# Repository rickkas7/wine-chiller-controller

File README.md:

# Wine chiller controller replacement

I have two Edgestar TWR282S thermoelectric wine chillers. One has wine in it, but the other I keep vegetables in, sort of like a root cellar.

They're over 10 years old, and I've been replacing parts on them for a while, but the case and doors are fine and the vegetable one has custom plexiglass shelves in it, so I hesitate to replace it.

I've replaced interior fans, [exterior fans](http://blog.rickk.com/food/2014/12/wine-chiller-exterior-fan-repair.html), and [Peltier chillers](http://blog.rickk.com/food/2013/06/repairing-a-wine-chiller.html), which are all pretty straightforward to do.

I also replaced the [controller boards](http://blog.rickk.com/food/2013/10/repairing-a-wine-chiller-part-2.html), which were available from Edgestar. They were kind of expensive at $48, and apparently not very durable, because one of the 4 year old replacements failed. And they're no longer available.

It appears the inductor failed. I might be able to just replace that but I have a better idea.

I added a new power supply, controller board, and a fancy display that shows the temperature and also communicates the data so I can monitor the temperatures remotely!

The cyan LED to the right of the alphanumeric display turns red when the temperature is out of normal range.

I also get push notifications on my phone if the temperature goes way out of normal range.

## Power Supply

I replaced the power supply with a $14.98 12V 10A switching power supply that I got [from Amazon](https://www.amazon.com/LEDMO-Switching-Converter-Adapter-Transformer/dp/B01E6RMASC/ref=pd_ybh_a_4). It really only needs to be 5 to 6A, but the 10A was reasonably priced and offers a nice safety margin.

I was able to use the existing power cord, and I just replaced the connector with two spade lugs for connecting to the power supply. I also moved it from above the Peltier heat sink to the side, so hot air is not constantly blowing across it. The old location really seems suboptimal.

## Power Board

I made a power/controller board as well. It has a power supply for the display board, a bunch of handy connectors, a fuse, and a relay. 

In practice the Peltier is always on in my experience, but I did add a relay so it could be turned off in software, based on the thermometer reading inside the chiller. This allows for temperature control, and would also save some energy, as the Peltier by far uses the most energy, about 48 watts.

This is the controller board with the 7 SMD components soldered to the board.

And with all of the through-hole components soldered on.

Installed in the chiller.

## Temperature sensor

I drilled a hole through the back of the chiller and used a weatherproof DS18B20 temperature sensor [from Amazon](https://www.amazon.com/Hilitchi-DS18B20-Waterproof-Temperature-Sensors/dp/B018KFX5X0/ref=sr_1_5). It was $12.99 for a set of 5 but I only needed 1 for this project.

## Interior connections

Above the temperature sensor is the wiring that goes to the interior control box. There is one connector with 2 red wires and a black. And another connector with a black and yellow.

Connect all of the reds together; these are the +12V to the light and interior fan.

Connect all of the blacks together; these are the GND to the light and interior fan.

The yellow wire is for the temperature control inside; that's not used.

The light switch still works.

## Display board

The display board is mounted on the front of the chiller.

Here's the display board with only the SMD components mounted. These include another DS18B20 temperature sensor (this time a 8-SOIC version) and a 4.7K pull-up resistor (0603 SMD) for the 1-Wire interface.

It also has a NeoPixel (WS2812) programmable LED and a 470 ohm series resistor for the data line (0603 SMD).

And power supply capacitors 0.1uF and 10 uF, and the SMD socket for the Particle Photon.

There are also through-hole connectors for a modular jack and a SSD1306 display.

## Total Materials

This did cost more than the original controller, but it has a lot more features. In reality, you can just buy the power supply and wire it up with wire nuts and a little wire and it would cost maybe $16.

| Item | Source | Price |
|---|---|---|
| Power Supply | [Amazon](https://www.amazon.com/LEDMO-Switching-Converter-Adapter-Transformer/dp/B01E6RMASC/ref=pd_ybh_a_4) | 14.98 |
| Spade Lugs (2) | | $0.20<sup>1</sup> |
| ChillerPower Board | [OshPark](https://oshpark.com) | $4.90<sup>2</sup> |
| 2-conductor terminal blocks (3) | [DigiKey](https://www.digikey.com/product-detail/en/on-shore-technology-inc/OSTTF020161/ED2623-ND/614572) | $2.55 |
| 3-conductor terminal block | [DigiKey](https://www.digikey.com/product-detail/en/on-shore-technology-inc/OSTTE030161/ED2636-ND/614585) | $1.00 | 
| Modular Jack | [DigiKey](https://www.digikey.com/product-detail/en/stewart-connector/SS-7066-NF/380-1043-ND/388305) | $0.77 |
| Fuse holder | [DigiKey](https://www.digikey.com/product-detail/en/keystone-electronics/3568/36-3568-ND/2137306) | $0.98 |
| Fuse MiniATC 7.5A |  | $0.76<sup>1</sup> |
| Capacitor 10 uF 0805 | [DigiKey](https://www.digikey.com/product-detail/en/murata-electronics-north-america/GRM21BR61C106KE15L/490-3886-1-ND/965928) | $0.07<sup>4</sup> |
| Capacitor 0.1 uF | [DigiKey](https://www.digikey.com/product-detail/en/murata-electronics-north-america/GRM188R71C104KA01D/490-1532-1-ND/587771) | $0.03<sup>3</sup> |
| Resistor 680 ohm 0805 | [DigiKey](https://www.digikey.com/product-detail/en/panasonic-electronic-components/ERJ-6GEYJ681V/P680ACT-ND/90033) | $0.01<sup>3</sup> |
| Green LED 0603 | [DigiKey](https://www.digikey.com/product-detail/en/lite-on-inc/LTST-C193KGKT-5A/160-1828-1-ND/2356247) | $0.23<sup>5</sup> |
| Relay | [DigiKey](https://www.digikey.com/product-detail/en/panasonic-electric-works/JS1-5V-F/255-2064-ND/1242012) | $1.63 |
| Diode BAS21 | [DigiKey](http://www.digikey.com/product-detail/en/BAS21-7-F/BAS21-FDICT-ND/717813) | $0.14 |
| 2N7002 MOSFET | [DigiKey](https://www.digikey.com/product-detail/en/on-semiconductor/2N7002LT3G/2N7002LT3GOSCT-ND/2704932) | $0.16 |
| R-78-E Regulator | [DigiKey](https://www.digikey.com/product-detail/en/recom-power/R-78E5.0-0.5/945-1648-5-ND/2834904) | $2.84 |
| DS18B20 Weatherproof | [Amazon](https://www.amazon.com/Hilitchi-DS18B20-Waterproof-Temperature-Sensors/dp/B018KFX5X0/ref=sr_1_5) | $2.99<sup>6</sup> |
| ChillerDisplay Board | [OshPark](https://oshpark.com) | $8.31<sup>8</sup> |
| Photon Headers (2) | [DigiKey](https://www.digikey.com/product-detail/en/sullins-connector-solutions/NPTC121KFXC-RC/S5604-ND/776062) | $3.38 |
| Particle Photon | [Amazon](https://www.amazon.com/Particle-PHOTON-Comprehensive-Development-Access/dp/B016YNU1A0/ref=pd_ybh_a_5) | $19.00 | 
| NeoPixel | [DigiKey](https://www.digikey.com/product-detail/en/adafruit-industries-llc/1655/1528-1104-ND/5154679) | $0.45<sup>7</sup> |
| SSD1306 Display | [eBay](https://www.ebay.com/itm/391742247377) | $5.45 |
| Resistor 470 ohm | [DigiKey](https://www.digikey.com/product-detail/en/panasonic-electronic-components/ERJ-3GEYJ471V/P470GCT-ND/134802) | $0.01<sup>3</sup> |
| Resistor 4.7K ohm | [DigiKey](https://www.digikey.com/product-detail/en/panasonic-electronic-components/ERJ-PA3J472V/P4.7KBZCT-ND/5036332) | $0.01<sup>3</sup> |
| Capacitor 10 uF 0805 | [DigiKey](https://www.digikey.com/product-detail/en/murata-electronics-north-america/GRM21BR61C106KE15L/490-3886-1-ND/965928) | $0.07<sup>4</sup> |
| Capacitor 0.1 uF | [DigiKey](https://www.digikey.com/product-detail/en/murata-electronics-north-america/GRM188R71C104KA01D/490-1532-1-ND/587771) | $0.03<sup>3</sup> |
| Modular Jack | [DigiKey](https://www.digikey.com/product-detail/en/stewart-connector/SS-7066-NF/380-1043-ND/388305) | $0.77 |
| Wire Nuts (gray) |  | $0.50<sup>1</sup> |
| Hook-up Wire 18ga |  | $0.50<sup>1</sup> |
| Modular cable (4 conductor) |  | $2.00<sup>1</sup> |

Total: $72.72

<sup>1</sup>I had these on hand, I just guessed the price.

<sup>2</sup>The ChillerPower board has a minimum order of 3 at OshPark, so the actual cost was $14.70.

<sup>3</sup>I bought these in quantity 100 and divided the price. If you bought them in single quantities they'd be around $0.10 each.

<sup>4</sup>I bought these in quantity 100 and divided the price. If you bought them in single quantities they'd be around $0.21 each.

<sup>5</sup>I bought these in quantity 25 and divided the price. If you bought them in single quantities they'd be around $0.41 each.

<sup>6</sup>I bought these in quantity 5 and divided the price. Other vendors sell them in single quantities at a higher price.

<sup>7</sup>I bought these in quantity 10 and divided the price. That's the smallest package they're sold in.

<sup>8</sup>The ChillerDisplay board has a minimum order of 3 at OshPark, so the actual cost was $24.95.

## Firmware

I haven't included the firmware for the Photon. It's a simple matter of programming. No really, it uses standard libraries for the DS18B20 and SSD1306 and it should't be complicated.

The problem is that my code relies on a bunch of server infrastructure that's too complicated to share, and I didn't feel like writing a new set of firmware just for this post that I'd never use. I may change my mind later.

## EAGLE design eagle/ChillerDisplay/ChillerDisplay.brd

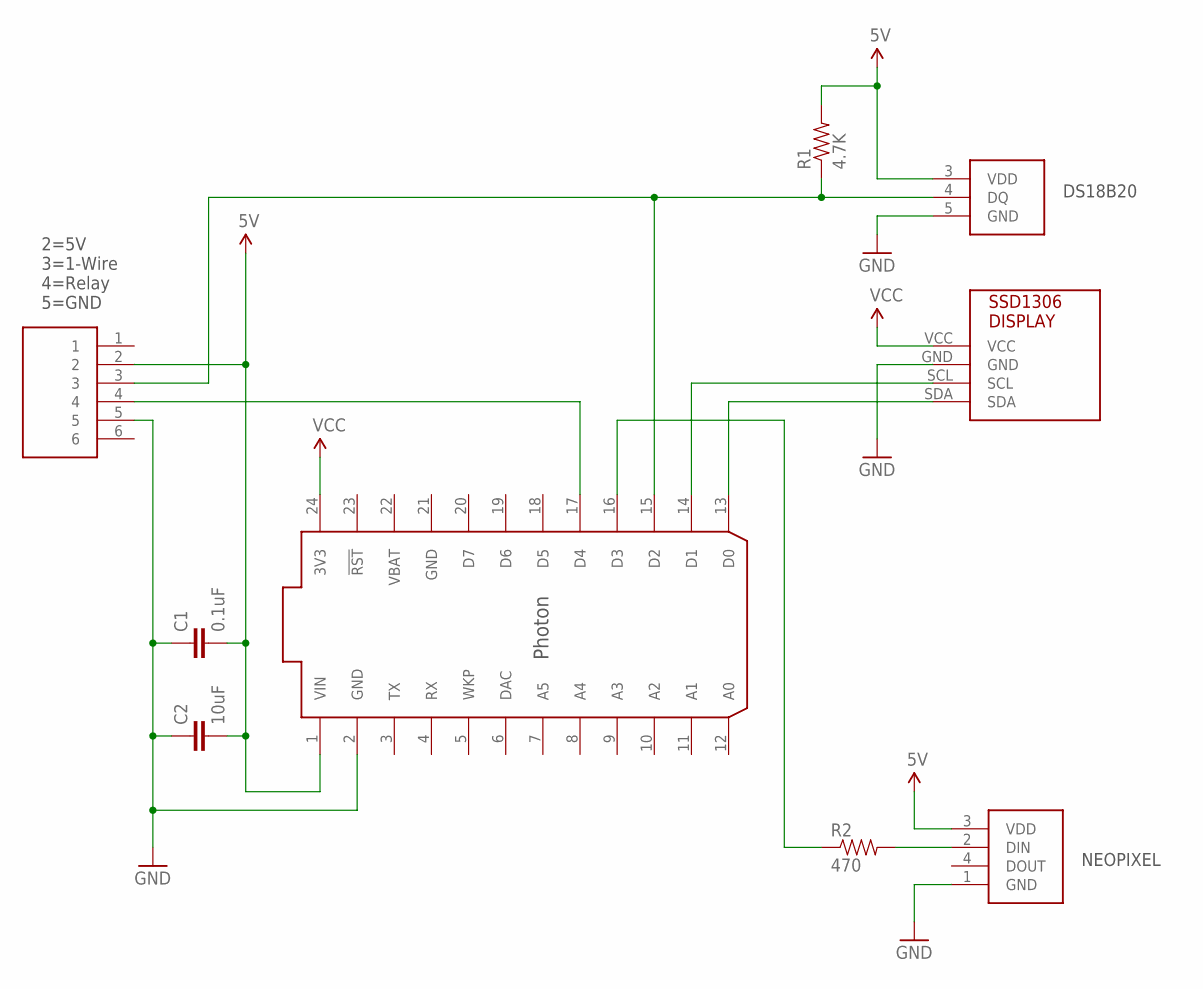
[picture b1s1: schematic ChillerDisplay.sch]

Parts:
C1: 0.1uF; 0603-CAP
C2: 10uF; 0603-CAP
J1: MODULAR-JACK-6P6C-1
R1: 4.7K; 0603-RES
R2: 470; 0603-RES
U$1: PHOTON; PHOTON-SMD
U$2: SSD1306REV-POL; SSD1306-REV-POL
U$3: DS18B208-SOIC; DS18B20-S0
U$4: SK6812

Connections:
5V: C1.2, C2.2, J1.2, R1.2, U$1.1 (VIN), U$3.3 (VDD), U$4.3 (VDD)
GND: C1.1, C2.1, J1.5, U$1.2 (GND), U$1.21 (GND), U$2.GND, U$3.5 (GND), U$4.1 (GND)
unnamed: U$1.13 (D0), U$2.SDA
unnamed: U$1.14 (D1), U$2.SCL
unnamed: J1.3, R1.1, U$1.15 (D2), U$3.4 (DQ)
unnamed: R2.2, U$4.2 (DIN)
unnamed: R2.1, U$1.16 (D3)
unnamed: J1.4, U$1.17 (D4)
VBAT: U$1.22 (VBAT)
VCC: U$1.24 (3V3), U$2.VCC

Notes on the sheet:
2=5V 3=1-Wire 4=Relay 5=GND
DS18B20
NEOPIXEL

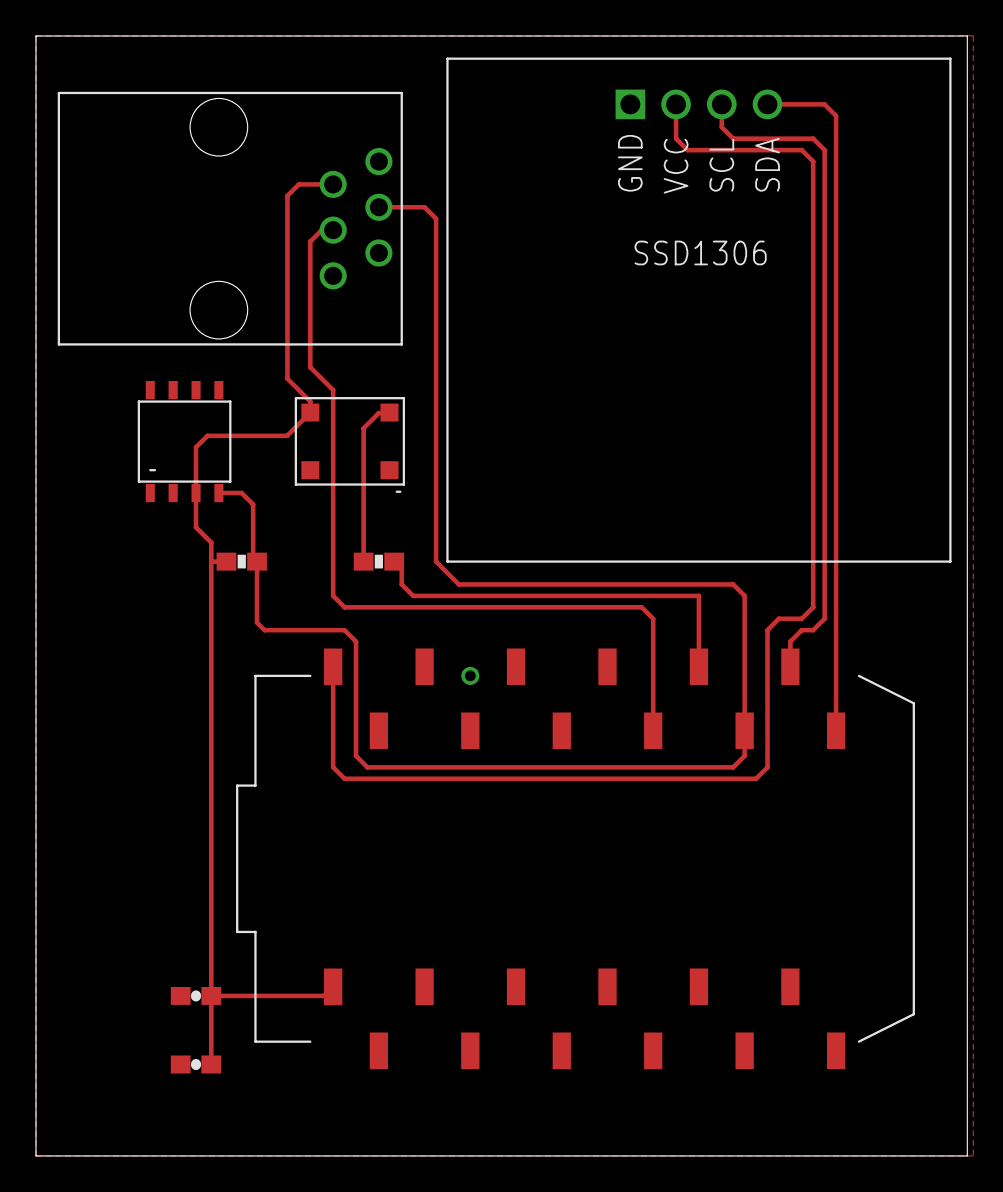
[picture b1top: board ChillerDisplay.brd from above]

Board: 2 copper layers, 51.7 x 62.2 mm, 9 parts (0 on the bottom side), 9 nets.

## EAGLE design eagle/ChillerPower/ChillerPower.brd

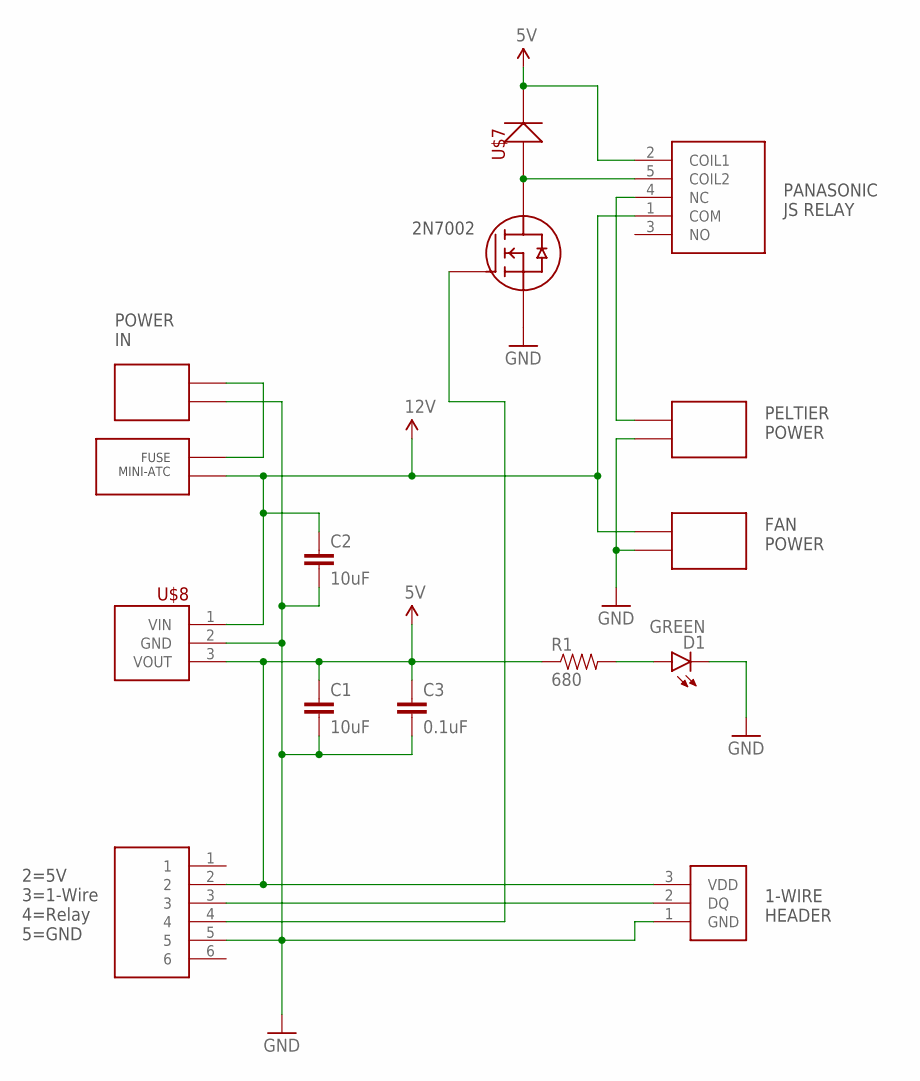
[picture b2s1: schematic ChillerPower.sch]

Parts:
C1, C2: 10uF; 0603-CAP
C3: 0.1uF; 0603-CAP
D1: GREEN; LED-0603
J1: MODULAR-JACK-6P6C-1
Q1: 2N7002L
R1: 680; 0805
U$1: FUSE-HOLDER-MINI-BLADE
U$2, U$4, U$5: TERMBLOCK-2X3.5MM
U$3: RELAY-PANASONIC-JS
U$6: TERMBLOCK-1WIRE
U$7: DIODE-BAS21
U$8: REG-R-78E

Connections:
5V: C1.1, C3.1, J1.2, R1.1, U$3.2 (COIL1), U$6.3 (VDD), U$7.3 (CA), U$8.3 (VOUT)
12V: C2.1, U$1.2, U$1.3 (2), U$3.1 (COM), U$5.1, U$8.1 (VIN)
GND: C1.2, C2.2, C3.2, D1.C, J1.5, Q1.2, U$2.2, U$4.2, U$5.2, U$6.1 (GND), U$8.2 (GND)
unnamed: U$1.1, U$1.4 (1), U$2.1
unnamed: Q1.3, U$3.5 (COIL2), U$7.1 (AN)
unnamed: J1.3, U$6.2 (DQ)
unnamed: U$3.4 (NC), U$4.1
unnamed: J1.4, Q1.1
unnamed: D1.A, R1.2

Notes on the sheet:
2=5V 3=1-Wire 4=Relay 5=GND
POWER IN
FAN POWER
PELTIER POWER
2N7002
1-WIRE HEADER
PANASONIC JS RELAY

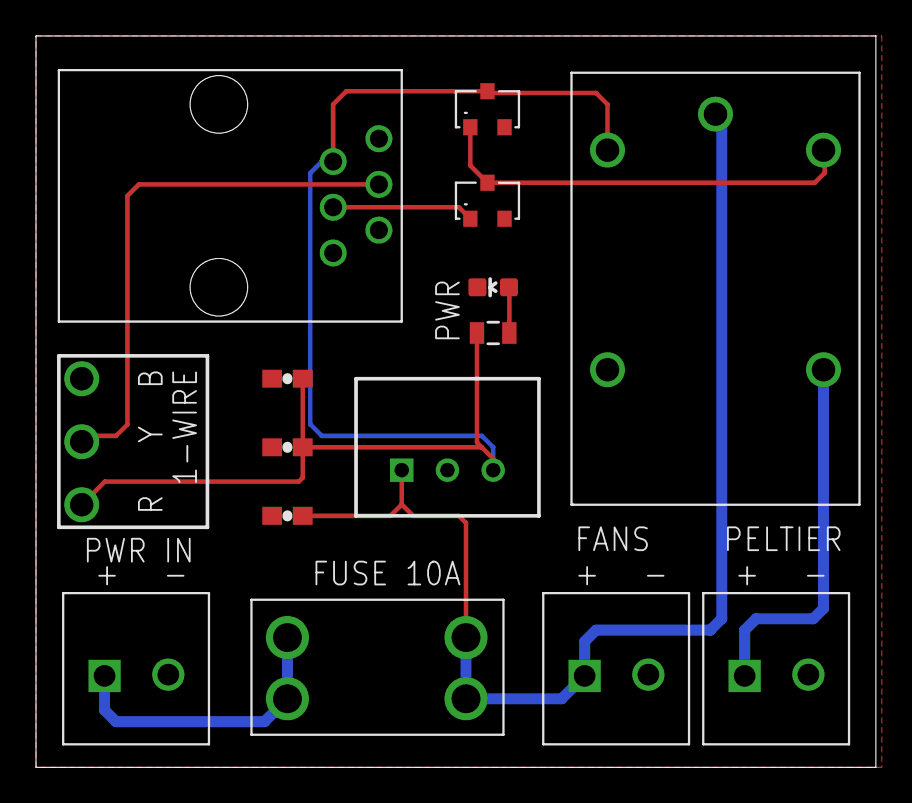
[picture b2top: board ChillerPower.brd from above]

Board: 2 copper layers, 46.7 x 40.6 mm, 15 parts (0 on the bottom side), 9 nets.

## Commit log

2017-10-24 initial checkin
2017-10-24 fix typo
